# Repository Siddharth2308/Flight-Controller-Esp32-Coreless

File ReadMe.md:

<br />
<div align="center">

## Flight Controller- Xiao ESP32S3
</div>

<!-- There are many great README templates available on GitHub; however, I didn't find one that really suited my needs so I created this enhanced one. I want to create a README template so amazing that it'll be the last one you ever need -- I think this is it.

Here's why:
* Your time should be focused on creating something amazing. A project that solves a problem and helps others
* You shouldn't be doing the same tasks over and over like creating a README from scratch
* You should implement DRY principles to the rest of your life :smile:

Of course, no one template will serve all projects since your needs may be different. So I'll be adding more in the near future. You may also suggest changes by forking this repo and creating a pull request or opening an issue. Thanks to all the people have contributed to expanding this template!

Use the `BLANK_README.md` to get started. -->

<p align="right">(<a href="#readme-top">back to top</a>)</p>

<!-- GETTING STARTED -->
<!-- ## Getting Started

This is an example of how you may give instructions on setting up your project locally.
To get a local copy up and running follow these simple example steps.

### Prerequisites

This is an example of how to list things you need to use the software and how to install them.
* npm
  ```sh
  npm install npm@latest -g
  ``` -->

<!-- ### Installation -->
<!-- 
_Below is an example of how you can instruct your audience on installing and setting up your app. This template doesn't rely on any external dependencies or services._

1. Get a free API Key at [https://example.com](https://example.com)
2. Clone the repo
   ```sh
   git clone https://github.com/your_username_/Project-Name.git
   ```
3. Install NPM packages
   ```sh
   npm install
   ```
4. Enter your API in `config.js`
   ```js
   const API_KEY = 'ENTER YOUR API';
   ```

<p align="right">(<a href="#readme-top">back to top</a>)</p> -->

<!-- USAGE EXAMPLES -->
<!-- ## Usage -->

<!-- Use this space to show useful examples of how a project can be used. Additional screenshots, code examples and demos work well in this space. You may also link to more resources.

_For more examples, please refer to the [Documentation](https://example.com)_

<p align="right">(<a href="#readme-top">back to top</a>)</p> -->

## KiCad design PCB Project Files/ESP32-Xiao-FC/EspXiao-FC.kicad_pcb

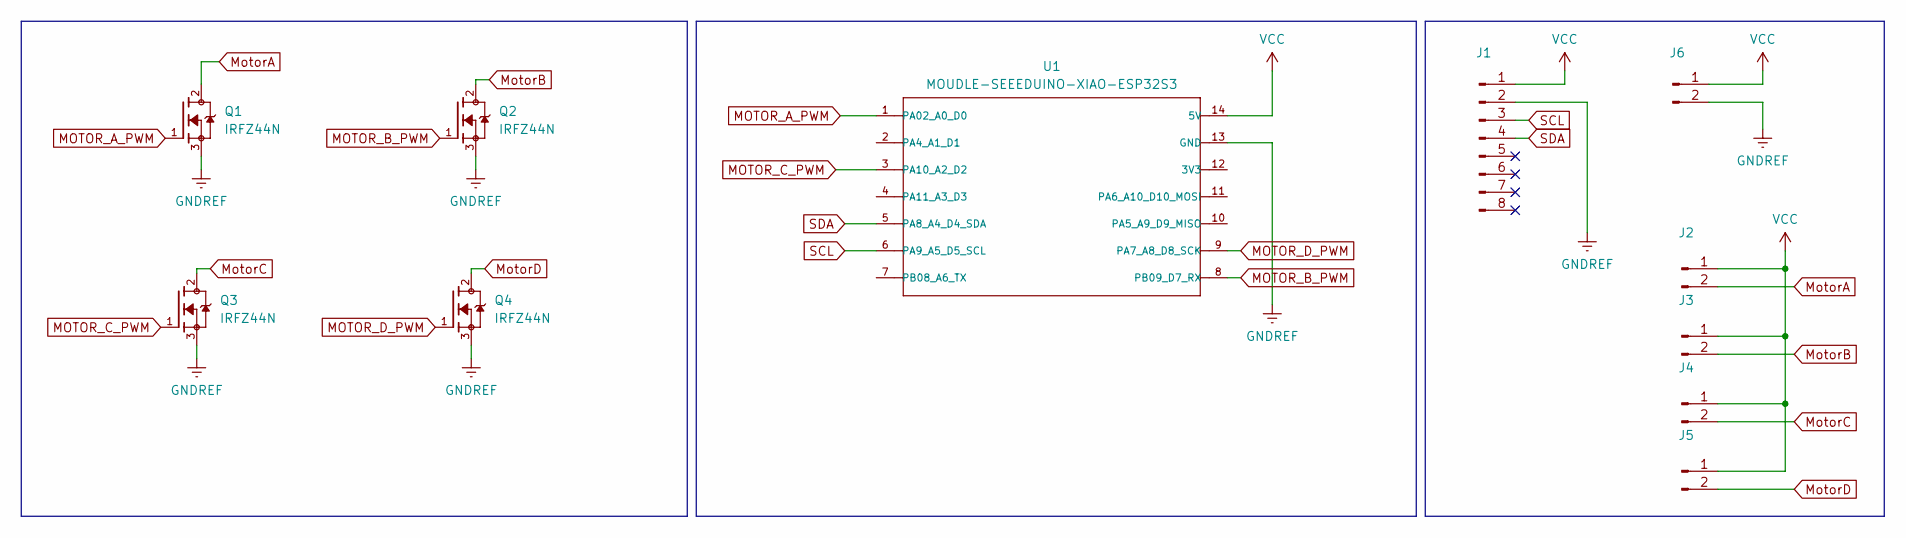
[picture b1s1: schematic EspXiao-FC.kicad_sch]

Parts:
J1: Conn_01x08_Pin; PinHeader_1x08_P2.54mm_Vertical
J2, J3, J4, J5, J6: Conn_01x02_Pin; PinHeader_1x02_P2.54mm_Vertical
Q1, Q2, Q3, Q4: IRFZ44N; irfz44n
U1: MOUDLE-SEEEDUINO-XIAO-ESP32S3; Xiao_esp32s3_sense

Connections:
GNDREF: J1.2, J6.2, Q1.3, Q2.3, Q3.3, Q4.3, U1.13 (GND)
MOTOR_A_PWM: Q1.1, U1.1 (PA02_A0_D0)
MOTOR_B_PWM: Q2.1, U1.8 (PB09_D7_RX)
MOTOR_C_PWM: Q3.1, U1.3 (PA10_A2_D2)
MOTOR_D_PWM: Q4.1, U1.9 (PA7_A8_D8_SCK)
MotorA: J2.2, Q1.2
MotorB: J3.2, Q2.2
MotorC: J4.2, Q3.2
MotorD: J5.2, Q4.2
SCL: J1.3, U1.6 (PA9_A5_D5_SCL)
SDA: J1.4, U1.5 (PA8_A4_D4_SDA)
VCC: J1.1, J2.1, J3.1, J4.1, J5.1, J6.1, U1.14 (5V)

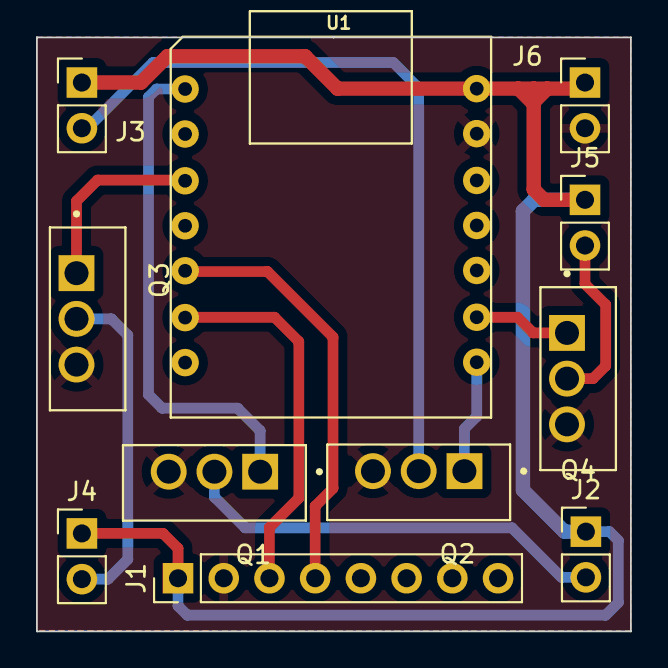
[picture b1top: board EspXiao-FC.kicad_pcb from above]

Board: 2 copper layers, 33.0 x 33.0 mm, 11 parts (0 on the bottom side), 12 nets.

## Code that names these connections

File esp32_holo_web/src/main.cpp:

#include <Arduino.h>
#include "SPIFFS.h"
#include <ESPAsyncWebServer.h>
#include <WiFi.h>
#include <WiFiUdp.h>
#include "soc/soc.h"
#include "soc/rtc_cntl_reg.h"

// #define ENABLE_ODOMETRY

#define PWM_RES 8
#define PWM_FREQ 1000
#define PWM_SETUP ledcSetup
#define PWM_ATTACH ledcAttachPin
#define SET_PWM ledcWrite

#define MA_CH 0
#define MB_CH 1
#define MC_CH 2
#define MD_CH 3
#define LIDAR_CH 4

#define MOTOR_A_PWM 26
#define MOTOR_B_PWM 27
#define MOTOR_C_PWM 5
#define MOTOR_D_PWM 23

#define LIDAR_PWM 25

#define MOTOR_A_DIR 2
#define MOTOR_B_DIR 4
#define MOTOR_C_DIR 32
#define MOTOR_D_DIR 33

#define MA_ENC_C1 13
#define MA_ENC_C2 39 //12

#define MB_ENC_C1 14
#define MB_ENC_C2 15

#define MC_ENC_C1 34
#define MC_ENC_C2 35

#define MD_ENC_C1 18
#define MD_ENC_C2 19

unsigned long last_packet = 0;

const char *ssid = "Test";
const char *password = "123456789";

const char* PARAM_INPUT_1 = "valX";
const char* PARAM_INPUT_2 = "valY";
const char* PARAM_INPUT_3 = "valW";

String inputMessage1;
String inputMessage2;
String inputMessage3;

int joy_x = 0, joy_y = 0, joy_w = 0;
float max_pwm = 90;
float val_x = 0.0F, val_y = 0.0F, val_w = 0.0f;
float mA_Speed, mB_Speed, mC_Speed, motorSpeedA, motorSpeedB, motorSpeedC;
void get_speed(float x, float y , float w);

volatile int count_A, count_B, count_C, count_D;

void drive();
void isr_A();
void isr_B();
void isr_C();
void isr_D();

bool keepSpinning = true;
//uint16_t debugPrintCounter = 0;
//const uint16_t debugPrintThreshold = 48; // print data every (this many) datapoints (if you are getting CRC errors, there may be buffer overflow, try setting this to like 48+ (or uncommenting printing entirely))
uint32_t debugPrintTimer;
const uint32_t dubugPrintInterval = 5000; // micros between prints

AsyncWebServer server(80);

void setup() {
  Serial.begin(115200);
  
  pinMode(MOTOR_A_PWM, OUTPUT);
  pinMode(MOTOR_B_PWM, OUTPUT);
  pinMode(MOTOR_C_PWM, OUTPUT);
  pinMode(MOTOR_D_PWM, OUTPUT);

  pinMode(LIDAR_PWM, OUTPUT);
  
  pinMode(MOTOR_A_DIR, OUTPUT);
  pinMode(MOTOR_B_DIR, OUTPUT);
  pinMode(MOTOR_C_DIR, OUTPUT);
  pinMode(MOTOR_D_DIR, OUTPUT);

  PWM_SETUP(MA_CH, PWM_FREQ, PWM_RES);
  PWM_SETUP(MB_CH, PWM_FREQ, PWM_RES);
  PWM_SETUP(MC_CH, PWM_FREQ, PWM_RES);
  PWM_SETUP(MD_CH, PWM_FREQ, PWM_RES);
  
  PWM_SETUP(LIDAR_CH, PWM_FREQ, PWM_RES);

  PWM_ATTACH(MOTOR_A_PWM, MA_CH);
  PWM_ATTACH(MOTOR_B_PWM, MB_CH);
  PWM_ATTACH(MOTOR_C_PWM, MC_CH);
  PWM_ATTACH(MOTOR_D_PWM, MD_CH);
  PWM_ATTACH(LIDAR_PWM, LIDAR_CH);

  // pinMode(MA_ENC_C2, INPUT);
  pinMode(MA_ENC_C1, INPUT_PULLUP);
  pinMode(MA_ENC_C2, INPUT);  
#ifdef ENABLE_ODOMETRY

  attachInterrupt(digitalPinToInterrupt(MA_ENC_C1), isr_A, FALLING);
  
  pinMode(MB_ENC_C1, INPUT_PULLUP);
  pinMode(MB_ENC_C2, INPUT_PULLUP);
  attachInterrupt(digitalPinToInterrupt(MB_ENC_C1), isr_B, FALLING);

  pinMode(MC_ENC_C1, INPUT_PULLUP);
  pinMode(MC_ENC_C2, INPUT_PULLUP);
  attachInterrupt(digitalPinToInterrupt(MC_ENC_C1), isr_C, FALLING);

  pinMode(MD_ENC_C1, INPUT_PULLUP);
  pinMode(MD_ENC_C2, INPUT_PULLUP);
  attachInterrupt(digitalPinToInterrupt(MD_ENC_C1), isr_D, FALLING);
#endif

  digitalWrite(MOTOR_A_DIR, LOW);
  digitalWrite(MOTOR_B_DIR, LOW);
  digitalWrite(MOTOR_C_DIR, LOW);
  digitalWrite(MOTOR_D_DIR, LOW);

  SET_PWM(MA_CH, 0);
  SET_PWM(MB_CH, 0);
  SET_PWM(MC_CH, 0);
  SET_PWM(MD_CH, 0);
  SET_PWM(LIDAR_CH, 255);

  Serial.println("PWM Setup Done");

// Server Code
  if (!SPIFFS.begin(true)){
    Serial.println("An Error has occurred while mounting SPIFFS");
    return;
  }

  Serial.println("SPIFFS Setup Done");

  // uint32_t brown_reg_temp = READ_PERI_REG(RTC_CNTL_BROWN_OUT_REG);
  // WRITE_PERI_REG(RTC_CNTL_BROWN_OUT_REG, 0);
  // WiFi.setTxPower(WIFI_POWER_MINUS_1dBm);
  // WRITE_PERI_REG(RTC_CNTL_BROWN_OUT_REG, brown_reg_temp);
  WRITE_PERI_REG(RTC_CNTL_BROWN_OUT_REG, 0);

  Serial.println("WiFi TX Power Limited");

  WiFi.softAP(ssid, password);
  // Connect to Wi-Fi
  // WiFi.begin(ssid, password);
  // while (WiFi.status() != WL_CONNECTED) {
  //   delay(1000);
  //   Serial.println("Connecting to WiFi..");
  // }
  
  Serial.println(WiFi.localIP());

  // IPAddress IP = WiFi.softAPIP();
  // Serial.print("AP IP address: ");
  // Serial.println(IP);

  server.on("/", HTTP_GET, [](AsyncWebServerRequest *request)
            { request->send(SPIFFS, "/joy.html", "text/html"); });

  server.on("/update", HTTP_GET, [] (AsyncWebServerRequest *request) {
    if (request->hasParam(PARAM_INPUT_1) && request->hasParam(PARAM_INPUT_2) && request->hasParam(PARAM_INPUT_3)) {
      inputMessage1 = request->getParam(PARAM_INPUT_1)->value();
      inputMessage2 = request->getParam(PARAM_INPUT_2)->value();
      inputMessage3 = request->getParam(PARAM_INPUT_3)->value();
      joy_x = inputMessage1.toInt();
      joy_y = inputMessage2.toInt();
      joy_w = inputMessage3.toInt();
      last_packet = millis();
    }
    else {
      inputMessage1 = "No message sent";
      inputMessage2 = "No message sent";
      inputMessage3 = "No message sent";
     }
    request->send(200, "text/plain", "OK");
  });

  server.begin();

  Serial.println("[eBot Mini] Esp32 Dev Board Initialized");
}

void loop() {
  // Serial.print("A: ");Serial.print(count_A);
  // Serial.print(" B: ");Serial.print(count_B);
  // Serial.print(" C: ");Serial.print(count_C);
  // Serial.print(" D: ");Serial.println(count_D);

  if(millis() - last_packet < 1000){
    val_x = (float)joy_x / 100.0F;
    val_y = (float)joy_y / 100.0F;

    if(abs(joy_y) > 50 && abs(joy_x) < 50){
      mA_Speed = val_y * 200;

      digitalWrite(MOTOR_A_DIR, mA_Speed < 0 ? LOW : HIGH);
      digitalWrite(MOTOR_B_DIR, mA_Speed < 0 ? LOW : HIGH);
      digitalWrite(MOTOR_C_DIR, mA_Speed < 0 ? LOW : HIGH);
      digitalWrite(MOTOR_D_DIR, mA_Speed < 0 ? LOW : HIGH);
 
      if(mA_Speed < 0) mA_Speed = -1 * mA_Speed;

      SET_PWM(MA_CH, mA_Speed);
      SET_PWM(MB_CH, mA_Speed);
      SET_PWM(MC_CH, mA_Speed);
      SET_PWM(MD_CH, mA_Speed);
    } else if(abs(joy_x) > 50 && abs(joy_y) < 50){
        mA_Speed = val_x * 200;

        digitalWrite(MOTOR_A_DIR, mA_Speed < 0 ? HIGH : LOW);
        digitalWrite(MOTOR_B_DIR, mA_Speed < 0 ? LOW : HIGH);
        digitalWrite(MOTOR_C_DIR, mA_Speed < 0 ? HIGH : LOW);
        digitalWrite(MOTOR_D_DIR, mA_Speed < 0 ? LOW : HIGH);

        if(mA_Speed < 0) mA_Speed = -1 * mA_Speed;

        SET_PWM(MA_CH, mA_Speed);
        SET_PWM(MB_CH, mA_Speed);
        SET_PWM(MC_CH, mA_Speed);
        SET_PWM(MD_CH, mA_Speed);
    } else {
        digitalWrite(MOTOR_A_DIR, LOW);
        digitalWrite(MOTOR_B_DIR, LOW);
        digitalWrite(MOTOR_C_DIR, LOW);
        digitalWrite(MOTOR_D_DIR, LOW);

        SET_PWM(MA_CH, 0);
        SET_PWM(MB_CH, 0);
        SET_PWM(MC_CH, 0);
        SET_PWM(MD_CH, 0);      
    }
  } else{
      digitalWrite(MOTOR_A_DIR, LOW);
      digitalWrite(MOTOR_B_DIR, LOW);
      digitalWrite(MOTOR_C_DIR, LOW);
      digitalWrite(MOTOR_D_DIR, LOW);

      SET_PWM(MA_CH, 80);
      SET_PWM(MB_CH, 80);
      SET_PWM(MC_CH, 80);
      SET_PWM(MD_CH, 80);
  } 
}

void drive(){

}

void get_speed(float x, float y , float w) {
  motorSpeedA = ( (x * (0.67)) + (y * 0) + (w * 0.33) );
  motorSpeedB = ( (x * (-0.33f)) + (y * (-0.58f)) + (w * 0.33) );
  motorSpeedC = ( (x * (-0.33f)) + (y * (0.58f))  + (w * 0.33) );

  mA_Speed = motorSpeedA * max_pwm;
  mB_Speed = motorSpeedB * max_pwm;
  mC_Speed = motorSpeedC * max_pwm;
}


void isr_A(){
  if(digitalRead(MA_ENC_C2)) count_A--;
  else count_A++;
}

void isr_B(){
  if(digitalRead(MB_ENC_C2)) count_B--;
  else count_B++;
}

void isr_C(){
  if(digitalRead(MC_ENC_C2)) count_C--;
  else count_C++;
}


void isr_D(){
  if(digitalRead(MD_ENC_C2)) count_D--;
  else count_D++;
}

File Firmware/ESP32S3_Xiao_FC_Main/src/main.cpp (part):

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  float motorC = throttle - PID_roll - PID_pitch;// - PID_yaw;
  float motorD = throttle + PID_roll - PID_pitch;// + PID_yaw;

  // if(motorA < 0) motorA = 0;
  // if(motorB < 0) motorB = 0;
  // if(motorC < 0) motorC = 0;
  // if(motorD < 0) motorD = 0;

  motor_speed_A = (int)motorA;
  motor_speed_B = (int)motorB;
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
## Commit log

2024-04-11 Complete
2024-04-15 hehe Suii
2024-04-18 Suuii
2024-05-14 Commit Before restructure
2024-05-14 Restructure
2024-07-03 PCB V1.1
2024-07-18 Joystick done
2025-06-27 Communication Fixed
2025-06-27 Restructuring
2025-07-25 Code
